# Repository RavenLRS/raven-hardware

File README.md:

# raven-hardware
Hardware designs for Raven
# MicroRX_RFM

The Files Provided are for your own use. 

The MicroRX_RFM uses a 4 layer PCB. 

This Readme is a work in Progress.....

## Getting Started

 I can be contacted on the Raven Slack or Telegram channels
 under user name: hdphilip
 
check with me if there are any updates 

### Prerequisites

What things you need to build the MicroRX_RFM.

 *  Hot Air Soldering station
 *  Experence in SMD soldering 402,602,QFN-48
 *  Good quality solder paste (I'm usuing TS391LT)

### Installing

Comming soon

## Authors

## License

This project is licensed under the MIT License - see the [LICENSE.md](LICENSE.md) file for details

## Acknowledgments

* Alberto

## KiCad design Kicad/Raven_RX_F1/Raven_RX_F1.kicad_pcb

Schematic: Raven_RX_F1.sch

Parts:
C1, C2: 10uF; C_0805_2012Metric_Pad1.15x1.40mm_HandSolder
C3: 100uF; C_0805_2012Metric_Pad1.15x1.40mm_HandSolder
D1: WS2812B; LED_WS2812B_PLCC4_5.0x5.0mm_P3.2mm
J1, J2: Conn_01x04_Female; PinHeader_1x04_P2.54mm_Vertical
J3: Conn_01x01_Female; Pad_1x01_P1.27mm
R1: 75; R_0805_2012Metric_Pad1.15x1.40mm_HandSolder
SW1: SW_Push; SW_3x4x2mm
U1: ESP32-WROOM; ESP32-WROOM-32
U2: E28-2G4M20S
U3: AMS1117-3.3; SOT-223-3_TabPin2

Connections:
+3V3: C2.1, C3.1, J2.2, R1.1, U1.2, U1.3, U2.1, U3.2 (VO)
/LED_VDD: D1.1, R1.2
GND: C1.2, C2.2, C3.2, D1.3, J1.1, J2.1, SW1.1, U1.1, U1.15, U1.38, U1.39, U2.2, U2.7, U2.10, U2.16, U3.1 (GND)
IO0=SW1: SW1.2, U1.25
IO4=DIO3: U1.26, U2.15
IO5=BUSY: U1.29, U2.12
IO13=RX: J1.3, U1.16
IO14=TX: J1.4, U1.13
IO15=A: J3.1, U1.23
IO16=DIO2: U1.27, U2.14
IO17=DIO1: U1.28, U2.13
IO18=NRESET: U1.30, U2.11
IO19=TX_EN: U1.31, U2.9
IO21=NSS: U1.33, U2.6
IO22=RX_EN: U1.36, U2.8
IO23=RGBLED: D1.4, U1.37
IO25=SCK: U1.10, U2.5
IO26=MOSI: U1.11, U2.4
IO27=MISO: U1.12, U2.3
RX0: J2.4, U1.34
TX0: J2.3, U1.35
VCC: C1.1, J1.2, U3.3 (VI)

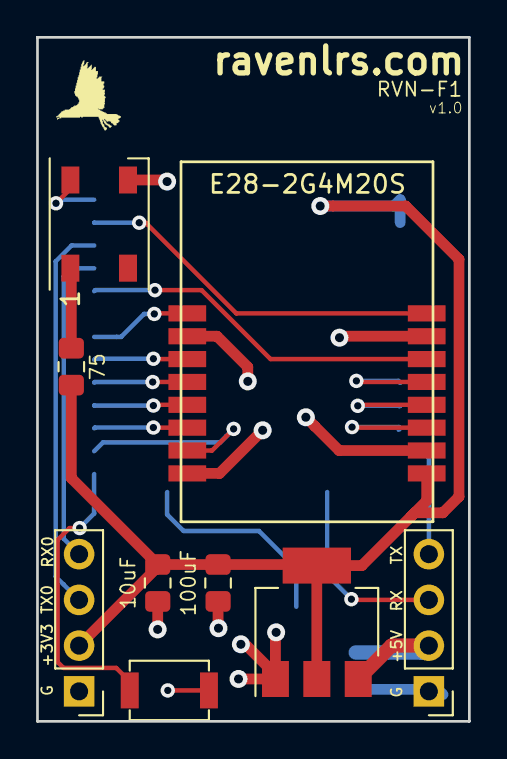
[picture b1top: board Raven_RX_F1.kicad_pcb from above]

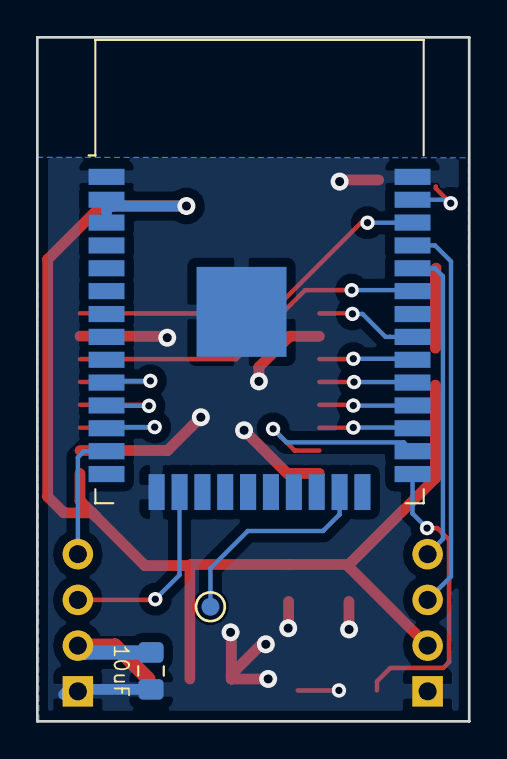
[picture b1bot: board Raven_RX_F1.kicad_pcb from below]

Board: 2 copper layers, 24.0 x 38.0 mm, 12 parts (3 on the bottom side), 22 nets.

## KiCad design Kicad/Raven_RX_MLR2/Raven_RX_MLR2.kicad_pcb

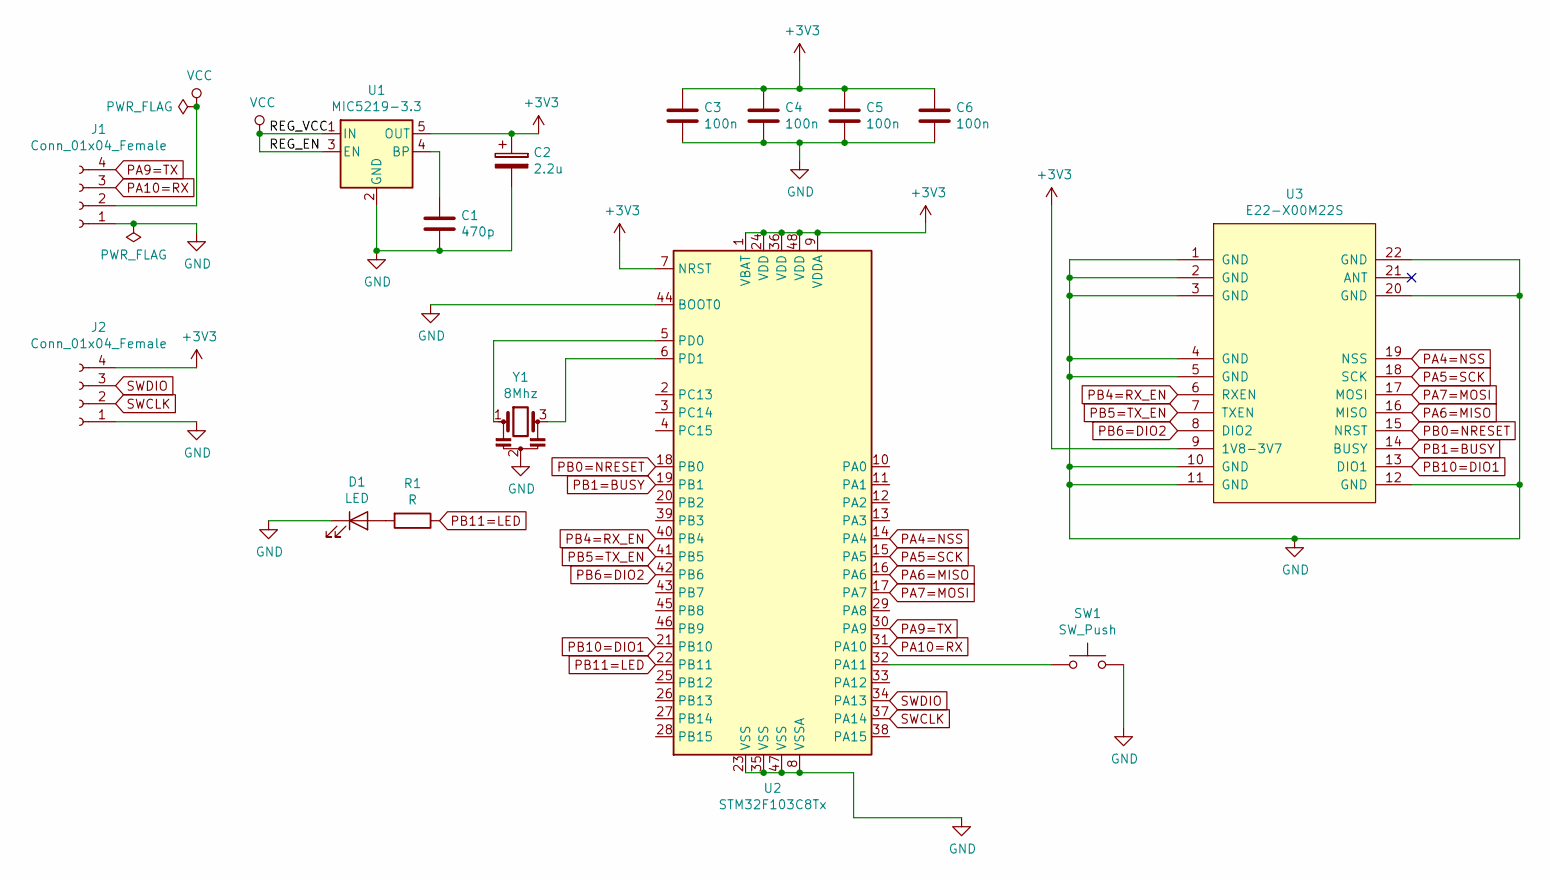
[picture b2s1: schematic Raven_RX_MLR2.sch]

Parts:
C1: 470p; C_0603_1608Metric_Pad1.05x0.95mm_HandSolder
C2: 2.2u; C_0603_1608Metric_Pad1.05x0.95mm_HandSolder
C3, C4, C5, C6: 100n; C_0603_1608Metric_Pad1.05x0.95mm_HandSolder
D1: LED; LED_0603_1608Metric_Pad1.05x0.95mm_HandSolder
J1: Conn_01x04_Female; PinHeader_1x04_P2.54mm_Vertical
J2: Conn_01x04_Female; PadHeader_1x04_P1.27mm
R1: R; R_0603_1608Metric_Pad1.05x0.95mm_HandSolder
SW1: SW_Push; SW_SPST_CK_KXT3
U1: MIC5219-3.3; SOT-23-5
U2: STM32F103C8Tx; LQFP-48_7x7mm_P0.5mm
U3: E22-X00M22S
Y1: 8Mhz; Resonator_SMD_muRata_CSTxExxV-3Pin_3.0x1.1mm

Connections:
+3V3: C2.1, C3.1, C4.1, C5.1, C6.1, J2.4, U1.5 (OUT), U2.1 (VBAT), U2.7 (NRST), U2.9 (VDDA), U2.24 (VDD), U2.36 (VDD), U2.48 (VDD), U3.9 (1V8-3V7)
GND: C1.2, C2.2, C3.2, C4.2, C5.2, C6.2, D1.1 (K), J1.1, J2.1, SW1.2, U1.2 (GND), U2.8 (VSSA), U2.23 (VSS), U2.35 (VSS), U2.44 (BOOT0), U2.47 (VSS), U3.1 (GND), U3.2 (GND), U3.3 (GND), U3.4 (GND), U3.5 (GND), U3.10 (GND), U3.11 (GND), U3.12 (GND), U3.20 (GND), U3.22 (GND), Y1.2
unnamed: C1.1, U1.4 (BP)
unnamed: D1.2 (A), R1.2
unnamed: SW1.1, U2.32 (PA11)
unnamed: U2.5 (PD0), Y1.1
unnamed: U2.6 (PD1), Y1.3
PA4=NSS: U2.14 (PA4), U3.19 (NSS)
PA5=SCK: U2.15 (PA5), U3.18 (SCK)
PA6=MISO: U2.16 (PA6), U3.16 (MISO)
PA7=MOSI: U2.17 (PA7), U3.17 (MOSI)
PA9=TX: J1.4, U2.30 (PA9)
PA10=RX: J1.3, U2.31 (PA10)
PB0=NRESET: U2.18 (PB0), U3.15 (NRST)
PB1=BUSY: U2.19 (PB1), U3.14 (BUSY)
PB4=RX_EN: U2.40 (PB4), U3.6 (RXEN)
PB5=TX_EN: U2.41 (PB5), U3.7 (TXEN)
PB6=DIO2: U2.42 (PB6), U3.8 (DIO2)
PB10=DIO1: U2.21 (PB10), U3.13 (DIO1)
PB11=LED: R1.1, U2.22 (PB11)
SWCLK: J2.2, U2.37 (PA14)
SWDIO: J2.3, U2.34 (PA13)
VCC: J1.2, U1.1 (IN), U1.3 (EN)

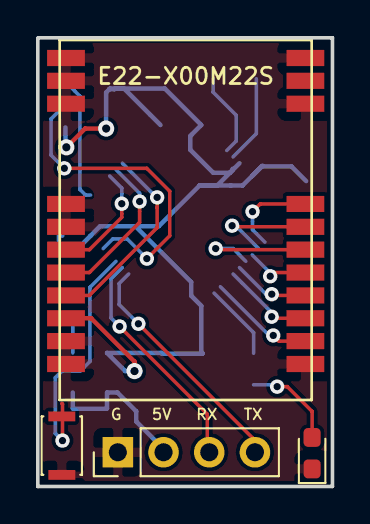
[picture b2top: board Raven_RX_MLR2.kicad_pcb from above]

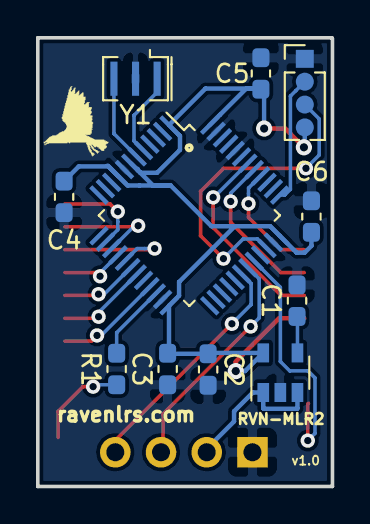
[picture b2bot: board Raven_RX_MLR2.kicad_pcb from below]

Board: 2 copper layers, 16.4 x 24.9 mm, 15 parts (11 on the bottom side), 23 nets.

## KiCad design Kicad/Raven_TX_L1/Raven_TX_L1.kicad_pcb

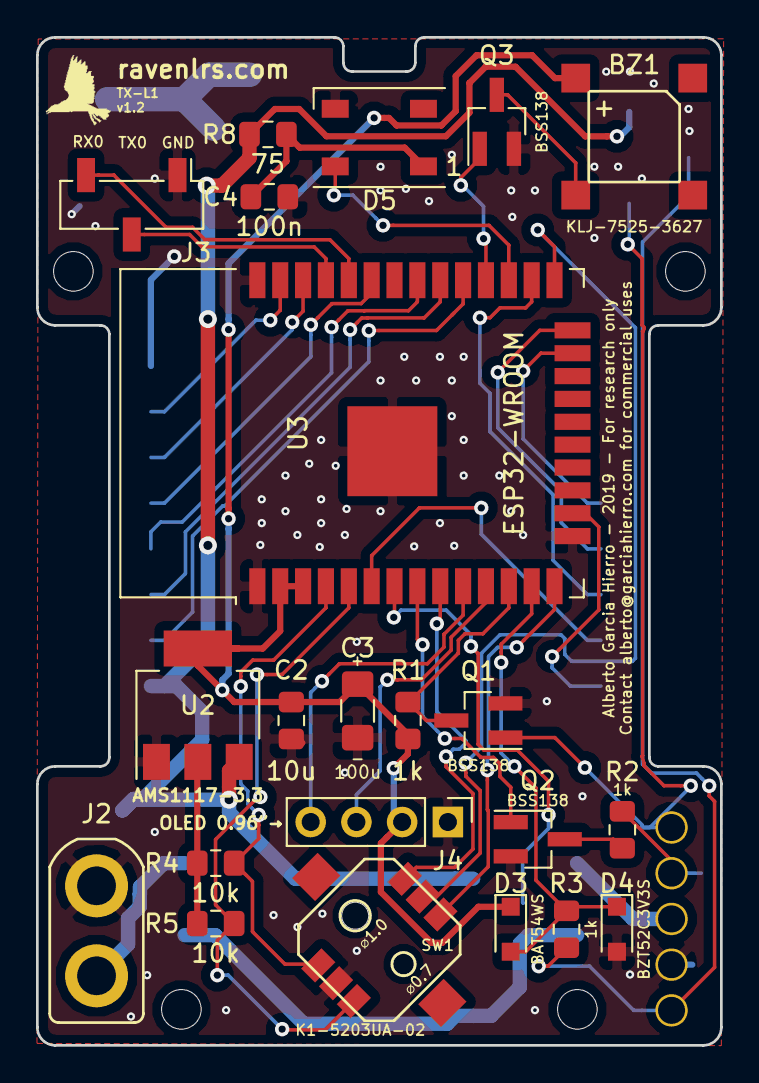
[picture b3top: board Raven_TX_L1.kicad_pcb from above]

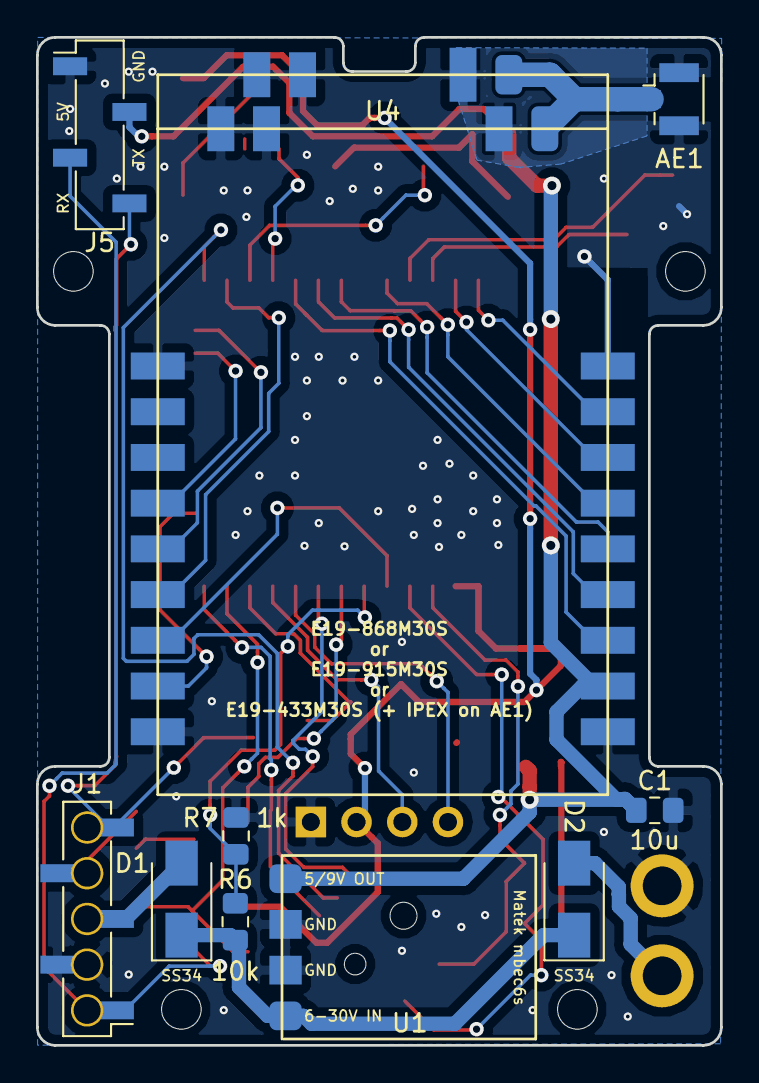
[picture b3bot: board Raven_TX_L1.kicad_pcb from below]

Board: 2 copper layers, 38.0 x 56.0 mm, 32 parts (10 on the bottom side), 39 nets.

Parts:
AE1: Antenna_Dipole; U.FL_Hirose_U.FL-R-SMT-1_Vertical
BZ1: KLJ-7525-3627
C1, C2: 10u; C_0805_2012Metric_Pad1.15x1.40mm_HandSolder
C3: 100u; C_1206_3216Metric_Pad1.42x1.75mm_HandSolder
C4: 100n; C_0805_2012Metric_Pad1.15x1.40mm_HandSolder
D1, D2: SS34; D_SMA
D3: BAT54WS; D_SOD-323_HandSoldering
D4: BZT52C3V3S; D_SOD-323_HandSoldering
D5: WS2812B; LED_WS2812B_PLCC4_5.0x5.0mm_P3.2mm
J1: Conn_JR; PinSocket_1x05_P2.54mm_Vertical_SMD_Pin1Left_WithHoles
J2: Battery; XT30
J3: Programming; PinSocket_1x03_P2.54mm_Vertical_SMD_Pin1Left
J4: Screen; PinHeader_1x04_P2.54mm_Vertical
J5: Conn_EXT_RX; PinSocket_1x04_P2.54mm_Vertical_SMD_Pin1Left
Q1, Q2, Q3: BSS138; SOT-23_Handsoldering
R1, R2, R3, R7: 1k; R_0805_2012Metric_Pad1.15x1.40mm_HandSolder
R4, R5, R6: 10k; R_0805_2012Metric_Pad1.15x1.40mm_HandSolder
R8: 75; R_0805_2012Metric_Pad1.15x1.40mm_HandSolder
SW1: K1-5203UA-02; K1-5203UA-0X
U1: MATEK_MBEC6S
U2: AMS1117-3.3; SOT-223-3_TabPin2
U3: ESP32-WROOM; ESP32-WROOM-32
U4: E19-XXXM30S; E19-433_868_915M30S

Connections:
+3V3: BZ1.1, C2.1, C3.1, D3.1, J4.2, R1.1, R4.1, R5.1, U2.2, U3.2, U3.3
+5V: C1.1, J5.2, R8.1, U1.1, U2.3, U4.11
/ANT: AE1.1, U4.19
/EXT_VBAT: D2.2, J2.2
/HEART_BEAT: J1.4, R2.2
/LED_RGB_5V: C4.1, D5.1, R8.2
/PXX_OUT: J1.5, J5.4, Q1.1
/SPORT: J1.1, J5.3, R3.2
/VBAT: D1.2, J1.3
GND: AE1.2, C1.2, C2.2, C3.2, C4.2, D4.2, D5.3, J1.2, J2.1, J3.1, J4.1, J5.1, Q1.2, Q2.2, Q3.2, R7.2, SW1.5, U1.2, U1.3, U2.1, U3.1, U3.15, U3.38, U3.39, U4.1, U4.9, U4.10, U4.18, U4.20, U4.21, U4.22
IO0=SW_PUSH: SW1.2, U3.25
IO2=DIO2: U3.24, U4.5
IO4=DIO1: U3.26, U4.6
IO5=SCK: U3.29, U4.12
IO12=SW_UP: SW1.1, U3.14
IO13=RST: U3.16, U4.8
IO14=SPORT: D3.2, D4.1, R3.1, U3.13
IO15=DIO3: U3.23, U4.4
IO16=RGBLED: D5.4, U3.27
IO17=BUZZER: Q3.1, U3.28
IO18=MISO: U3.30, U4.13
IO19=MOSI: U3.31, U4.14
IO21=NSS: U3.33, U4.15
IO22=TXEN: U3.36, U4.16
IO23=RXEN: U3.37, U4.17
IO25=SCREEN_SDA: J4.4, U3.10
IO26=SCREEN_SCL: J4.3, U3.11
IO27=PXX_OUT_INV: Q1.3, R1.2, U3.12
IO32=HEARTBEAT: Q2.1, U3.8
IO33=SW_LEFT: SW1.3, U3.9
IO34=DIO0: U3.6, U4.7
IO35=VCC_ADC: R6.2, R7.1, U3.7
IO36=SW_DOWN: R4.2, SW1.6, U3.4
IO39=SW_RIGHT: R5.2, SW1.4, U3.5
unnamed: BZ1.2, Q3.3
unnamed: Q2.3, R2.1
RX0: J3.3, U3.34
TX0: J3.2, U3.35
VCC: D1.1, D2.1, R6.1, U1.4

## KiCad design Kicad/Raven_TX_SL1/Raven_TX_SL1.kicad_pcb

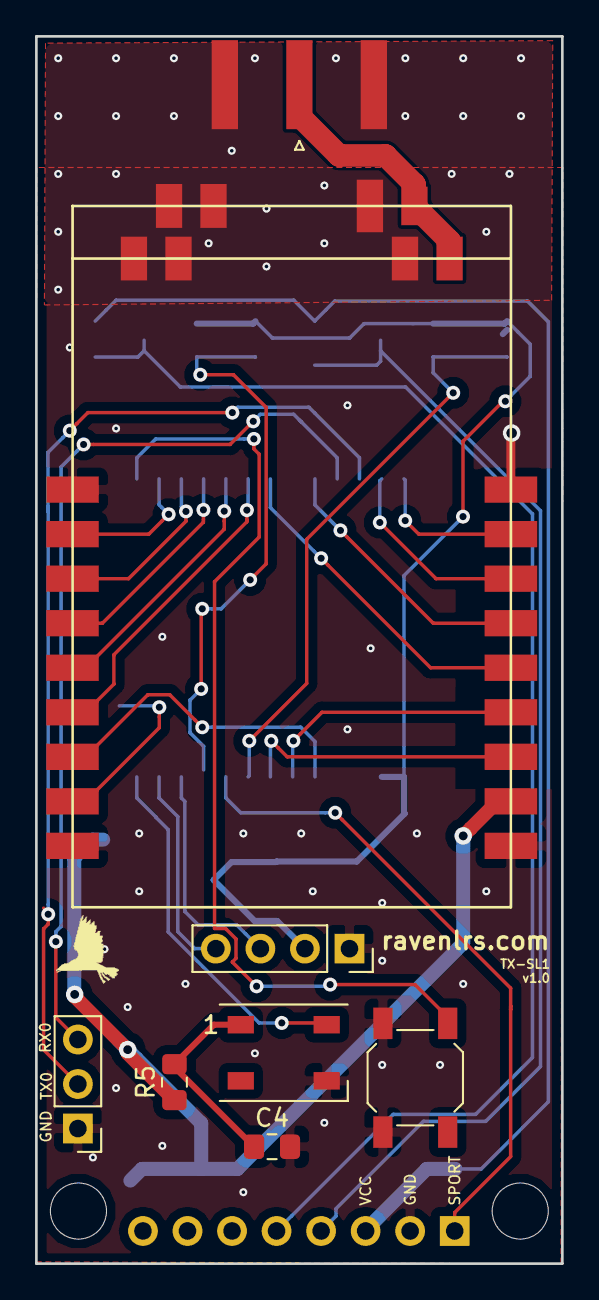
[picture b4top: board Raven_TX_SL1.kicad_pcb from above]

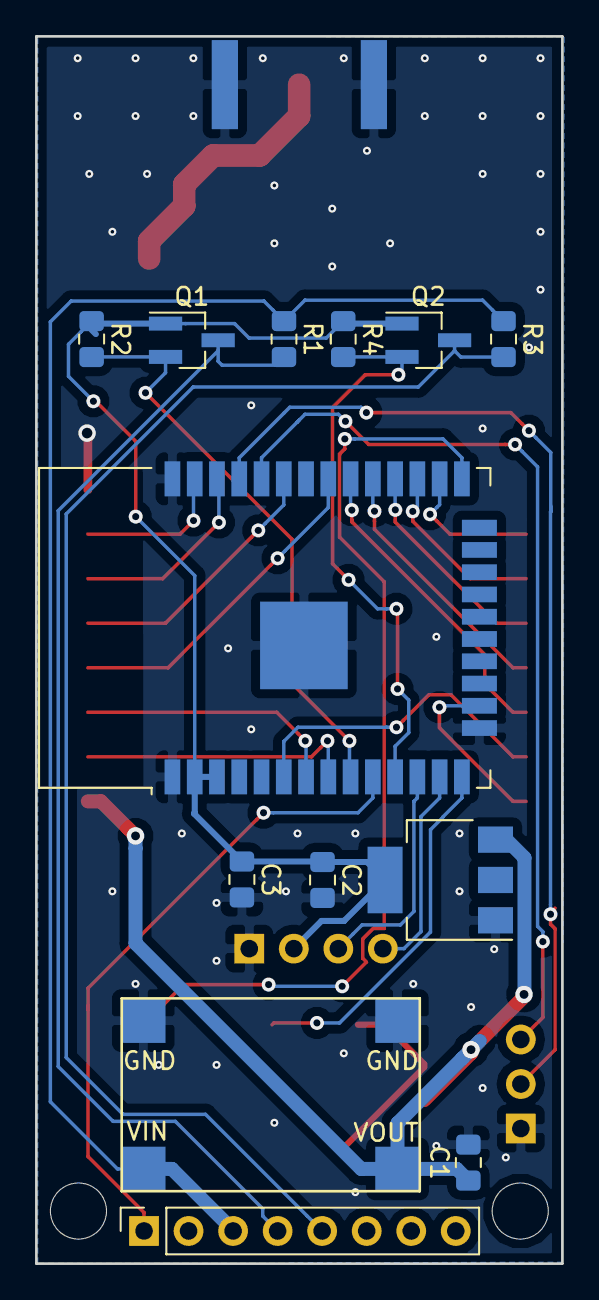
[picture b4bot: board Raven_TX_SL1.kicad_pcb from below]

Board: 2 copper layers, 30.0 x 70.0 mm, 21 parts (13 on the bottom side), 30 nets.

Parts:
AE1: Antenna_Dipole; SMA_Amphenol_132289_EdgeMount
C1, C2: 10u; C_0805_2012Metric_Pad1.15x1.40mm_HandSolder
C3: 100u; C_0805_2012Metric_Pad1.15x1.40mm_HandSolder
C4: 100n; C_0805_2012Metric_Pad1.15x1.40mm_HandSolder
D1: WS2812B; LED_WS2812B_PLCC4_5.0x5.0mm_P3.2mm
J1: Conn_XLite; PinSocket_1x08_P2.54mm_Vertical
J2: Programming; PinHeader_1x03_P2.54mm_Vertical
J3: Screen; PinSocket_1x04_P2.54mm_Vertical
Q1, Q2: Q_NMOS_GSD; SOT-23_Handsoldering
R1, R2, R3, R4: 10k; R_0805_2012Metric_Pad1.15x1.40mm_HandSolder
R5: 75; R_0805_2012Metric_Pad1.15x1.40mm_HandSolder
SW1: SW_Push; SW_SPST_SKQG_WithStem
U1: BEC; 5VBEC
U2: AMS1117-3.3; SOT-223-3_TabPin2
U3: ESP32-WROOM; ESP32-WROOM-32
U4: E19-XXXM30S; E19-433_868_915M30S

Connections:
+3V3: C2.1, C3.1, J3.2, Q1.1, Q2.1, R2.1, R4.1, U2.2, U3.2, U3.3
+5V: C1.1, R5.1, U1.3, U2.3, U4.11
/ANT: AE1.1, U4.19
/HEART_BEAT: J1.4, Q1.3, R1.2
/LED_RGB_5V: C4.1, D1.1, R5.2
/PXX_OUT: J1.5, Q2.3, R3.2
GND: AE1.2, C1.2, C2.2, C3.2, C4.2, D1.3, J1.2, J2.1, J3.1, SW1.1, U1.2, U1.4, U2.1, U3.1, U3.15, U3.38, U3.39, U4.1, U4.9, U4.10, U4.18, U4.20, U4.21, U4.22
IO0=SW1: SW1.2, U3.25
IO4=DIO5: U3.26, U4.2
IO5=DIO2: U3.29, U4.5
IO12=RGBLED: D1.4, U3.14
IO13=RST: U3.16, U4.8
IO14=SCREEN_SDA: J3.4, U3.13
IO16=DIO4: U3.27, U4.3
IO17=DIO3: U3.28, U4.4
IO18=DIO1: U3.30, U4.6
IO19=MOSI: U3.31, U4.14
IO21=NSS: U3.33, U4.15
IO22=TXEN: U3.36, U4.16
IO23=RXEN: U3.37, U4.17
IO25=SPORT: J1.1, U3.10
IO26=PXX_OUT_3V3: Q2.2, R4.2, U3.11
IO27=SCREEN_SCL: J3.3, U3.12
IO32=SCK: U3.8, U4.12
IO33=HEART_BEAT_3V3: Q1.2, R2.2, U3.9
IO34=DIO0: U3.6, U4.7
IO35=MISO: U3.7, U4.13
RX0: J2.3, U3.34
TX0: J2.2, U3.35
VCC: J1.3, R1.1, R3.1, U1.1

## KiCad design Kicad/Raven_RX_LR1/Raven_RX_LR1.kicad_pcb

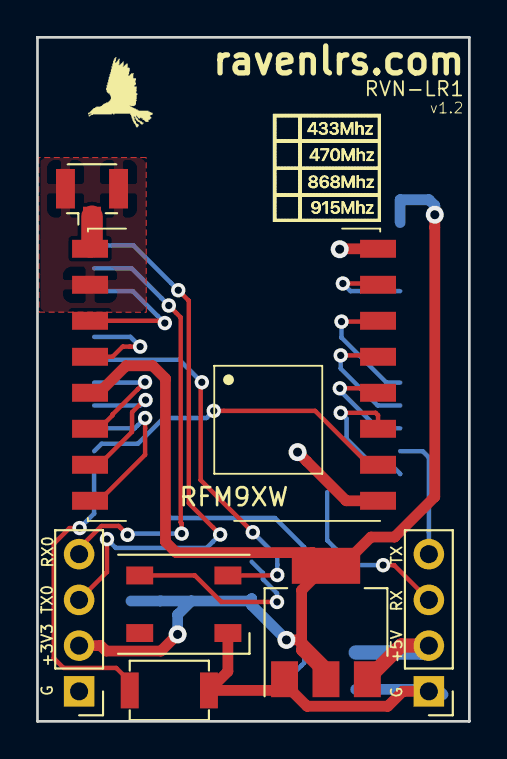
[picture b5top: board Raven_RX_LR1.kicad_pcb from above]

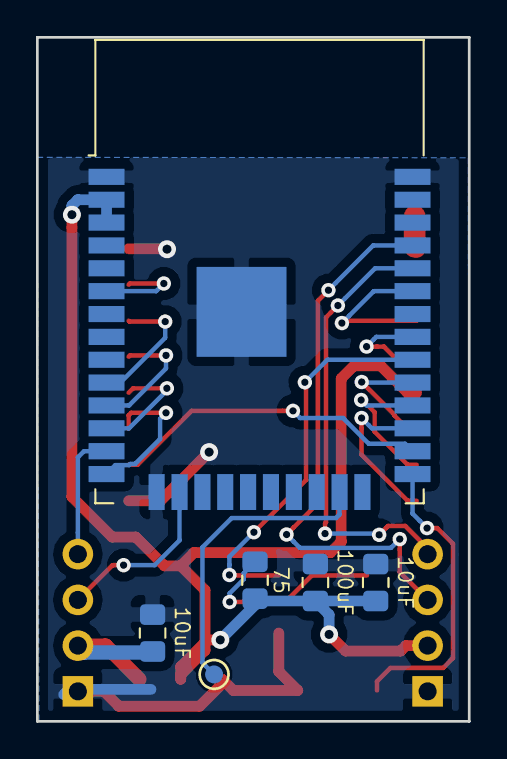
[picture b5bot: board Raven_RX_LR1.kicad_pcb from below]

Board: 2 copper layers, 24.0 x 38.0 mm, 14 parts (6 on the bottom side), 24 nets.

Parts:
AE1: Antenna_Dipole; U.FL_Hirose_U.FL-R-SMT-1_Vertical
C1, C2: 10uF; C_0805_2012Metric_Pad1.15x1.40mm_HandSolder
C3: 100uF; C_0805_2012Metric_Pad1.15x1.40mm_HandSolder
D1: WS2812B; LED_WS2812B_PLCC4_5.0x5.0mm_P3.2mm
J1, J2: Conn_01x04_Female; PinHeader_1x04_P2.54mm_Vertical
J3: Conn_01x01_Female; Pad_1x01_P1.27mm
LOGO: Freqs_433_470_868_915
R1: 75; R_0805_2012Metric_Pad1.15x1.40mm_HandSolder
SW1: SW_Push; SW_3x4x2mm
U1: ESP32-WROOM; ESP32-WROOM-32
U2: RFM98W-433S2; HOPERF_RFM9XW_SMD
U3: AMS1117-3.3; SOT-223-3_TabPin2

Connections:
+3V3: C2.1, C3.1, J2.2, R1.1, U1.2, U1.3, U2.13, U3.2
/LED_VDD: D1.1, R1.2
GND: C1.2, C2.2, C3.2, D1.3, J1.1, J2.1, SW1.1, U1.1, U1.15, U1.38, U1.39, U2.1, U2.8, U3.1
IO0=SW1: SW1.2, U1.25
IO4=MISO: U1.26, U2.2
IO5=DIO0: U1.29, U2.14
IO12=MOSI: U1.14, U2.3
IO13=RX: J1.3, U1.16
IO14=TX: J1.4, U1.13
IO15=A: J3.1, U1.23
IO16=DIO2: U1.27, U2.16
IO17=DIO1: U1.28, U2.15
IO18=LED_RGB: D1.4, U1.30
IO19=DIO4: U1.31, U2.12
IO21=DIO3: U1.33, U2.11
IO25=RESET: U1.10, U2.6
IO26=NSS: U1.11, U2.5
IO27=SCK: U1.12, U2.4
IO34=DIO5: U1.6, U2.7
unnamed: AE1.1, U2.9
unnamed: AE1.2, U2.10
RX0: J2.4, U1.34
TX0: J2.3, U1.35
VCC: C1.1, J1.2, U3.3

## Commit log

2018-10-27 Update RX/MicroRX_RFM/MicroRX_Schematic.pdf
    Added Schematic for the MicroRX RFM project
2018-10-28 added PCB layout files
    added PCB layout files
2018-10-28 Update RX/MicroRX_RFM/MicroRX_Gerbers.zip
    added silkscreen part info, changed R5,R6 to 602 from 402
2018-10-28 Update files name
    added information to the Schematic
2018-10-28 updated Layout
2018-10-28 updated BOM
2018-11-03 Update RX/AFnano
2018-11-04 1 watt tx jr style TX
2018-11-05 Update Readme.md
    update readme for new revision MicroRX_RFM
2018-11-06 Remove bmp, add png
2018-11-11 Replace rar with zip
2018-11-11 Replace image with wrong text.
2018-12-04 Create Readme_CN.md
    AFnano的中文简介
2019-01-14 Upload gerbers and BOM
2019-01-14 Upload pictures of top and bottom
2019-01-25 Add a cases for Frsky X9D
2019-06-20 Add Kicad projects for several TX and RX
